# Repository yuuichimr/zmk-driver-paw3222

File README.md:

# ZMK PAW3222 Driver

This driver enables the use of the PIXART PAW3222 optical sensor with the ZMK framework.

## Overview

The PAW3222 is a low-power optical mouse sensor suitable for tracking applications such as mice and trackballs. This driver communicates with the PAW3222 sensor via SPI interface.

## Installation

1. Add as a ZMK module in your west.yml:

```
manifest:
  remotes:
    - name: zmkfirmware
      url-base: https://github.com/zmkfirmware
    - name: sekigon-gonnoc
      url-base: https://github.com/sekigon-gonnoc
  projects:
    - name: zmk
      remote: zmkfirmware
      revision: main
      import: app/west.yml
    - name: zmk-driver-paw3222
      remote: sekigon-gonnoc
      revision: main
```

## Device Tree Configuration

Configure in your shield or board config file (.overlay or .dtsi):

```dts
&pinctrl {
    spi0_default: spi0_default {
        group1 {
            psels = <NRF_PSEL(SPIM_SCK, 0, 12)>,
                <NRF_PSEL(SPIM_MOSI, 1, 9)>,
                <NRF_PSEL(SPIM_MISO, 1, 9)>;
        };
    };

    spi0_sleep: spi0_sleep {
        group1 {
            psels = <NRF_PSEL(SPIM_SCK, 0, 12)>,
                <NRF_PSEL(SPIM_MOSI, 1, 9)>,
                <NRF_PSEL(SPIM_MISO, 1, 9)>;
            low-power-enable;
        };
    };
};

&spi0 {
    status = "okay";
    compatible = "nordic,nrf-spim";
    pinctrl-0 = <&spi0_default>;
    pinctrl-1 = <&spi0_sleep>;
    pinctrl-names = "default", "sleep";
    cs-gpios = <&gpio0 13 GPIO_ACTIVE_LOW>;

    trackball: trackball@0 {
        status = "okay";
        compatible = "pixart,paw3222";
        reg = <0>;
        spi-max-frequency = <2000000>;
        irq-gpios = <&gpio0 15 GPIO_ACTIVE_LOW>;
    };
};
```

## Enable the module in your keyboard's Kconfig file

Add the following to your keyboard's `Kconfig.defconfig`:

```kconfig
if ZMK_KEYBOARD_YOUR_KEYBOARD

config ZMK_POINTING
    default y

config PAW3222
    default y

endif
```

## Properties

- `irq-gpios`: GPIO connected to the motion pin (required)
- `power-gpios`: GPIO that switches the sensor supply (optional)
- `res-cpi`: CPI resolution for the sensor (optional)
- `force-awake`: Initialize the sensor in "force awake" mode (optional, boolean)

## Kconfig

- `CONFIG_PAW3222_POLL_INTERVAL_MS` (default `15`, range 4-50): polling interval used
  while the sensor keeps reporting motion. Lower = smoother cursor, slightly more current.

## Notes

- Works with `CONFIG_PM_DEVICE_RUNTIME=y`: the driver takes a runtime-PM reference
  at init, so the sensor is no longer left suspended (previously it never reported
  motion when runtime PM was enabled).

## Example keyboard

[`keyboard/`](keyboard/) contains **Tsumugi**, an open low-profile wireless split
keyboard with a PAW3222 trackball built on this driver (PCB, case, ZMK firmware).

---

# ZMK PAW3222 ドライバ

このドライバは、PIXART PAW3222光学センサーをZMKフレームワークで使用できるようにします。

## 概要

PAW3222は、マウスやトラックボールなどのトラッキングアプリケーションに適した低消費電力の光学マウスセンサーです。このドライバはSPIインターフェースを介してPAW3222センサーと通信します。

## インストール

1. ZMKモジュールとして追加：

```
# west.yml に追加
manifest:
  remotes:
    - name: zmkfirmware
      url-base: https://github.com/zmkfirmware
    - name: sekigon-gonnoc
      url-base: https://github.com/sekigon-gonnoc
  projects:
    - name: zmk
      remote: zmkfirmware
      revision: main
      import: app/west.yml
    - name: zmk-driver-paw3222
      remote: sekigon-gonnoc
      revision: main
```

## デバイスツリー設定

シールドまたはボード設定ファイル（.overlayまたは.dtsi）で設定：

```dts
&pinctrl {
    spi0_default: spi0_default {
        group1 {
            psels = <NRF_PSEL(SPIM_SCK, 0, 12)>,
                <NRF_PSEL(SPIM_MOSI, 1, 9)>,
                <NRF_PSEL(SPIM_MISO, 1, 9)>;
        };
    };

    spi0_sleep: spi0_sleep {
        group1 {
            psels = <NRF_PSEL(SPIM_SCK, 0, 12)>,
                <NRF_PSEL(SPIM_MOSI, 1, 9)>,
                <NRF_PSEL(SPIM_MISO, 1, 9)>;
            low-power-enable;
        };
    };
};

&spi0 {
    status = "okay";
    compatible = "nordic,nrf-spim";
    pinctrl-0 = <&spi0_default>;
    pinctrl-1 = <&spi0_sleep>;
    pinctrl-names = "default", "sleep";
    cs-gpios = <&gpio0 13 GPIO_ACTIVE_LOW>;

    trackball: trackball@0 {
        status = "okay";
        compatible = "pixart,paw3222";
        reg = <0>;
        spi-max-frequency = <2000000>;
        irq-gpios = <&gpio0 15 GPIO_ACTIVE_LOW>;
    };
};
```

## キーボードのKconfigファイルでモジュールを有効化

キーボードの `Kconfig.defconfig` に以下を追加：

```kconfig
if ZMK_KEYBOARD_YOUR_KEYBOARD

config ZMK_POINTING
    default y

config PAW3222
    default y

endif
```

## プロパティ

- `irq-gpios`: モーションピンに接続されたGPIO（必須）
- `power-gpios`: センサー電源を切り替えるGPIO（任意）
- `res-cpi`: センサーのCPI解像度（任意）
- `force-awake`: センサーを「強制起動」モードで初期化（任意、ブール値）

## Kconfig

- `CONFIG_PAW3222_POLL_INTERVAL_MS`（既定 `15`、4〜50）: 動き検出中のポーリング間隔。
  小さいほどカーソルが滑らかになり、消費電流はわずかに増えます。

## 補足

- `CONFIG_PM_DEVICE_RUNTIME=y` でも動作します。初期化時にランタイムPMの参照を取得するため、
  以前のように「ランタイムPM有効時にセンサーがサスペンドされたまま動かない」問題は起きません。

## 作例キーボード

[`keyboard/`](keyboard/) に、このドライバを使ったロープロファイル無線分割トラックボールキーボード
**Tsumugi（紡）** の設計一式（PCB・ケース・ZMKファームウェア）があります。

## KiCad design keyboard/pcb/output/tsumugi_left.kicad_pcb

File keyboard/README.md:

# Tsumugi（紡）— ロープロファイル無線分割トラックボールキーボード

> **紡（つむぎ）**: 左右ふたつの手を、ひとつのキーボードへ「紡ぐ」。
> 分割にも一体型にもなり、ボール・トラックパッド・エンコーダー・ブランクを自由に差し替えられる。

Tsumugi は、moNa2 / roBa / Keyball44 / 小人キー / 双掌（SO-SHO）/ Toucan / torabo-tsuki など、
いま手に入る「トラックボール付き分割キーボード」の良いところを整理し、
それぞれの弱点をまとめて解消することを目標に設計した **オープンソースの分割キーボード** です。
PCB・ケース・ファームウェア・キーマップ・製造データまで、すべてこのディレクトリから再生成できます。

> ⚠️ **ステータス: 設計 v0.1（試作前）** — ファームウェアは全バリアントのビルド成功、
> PCB は KiCad DRC エラー 0 / 未配線 0 を確認済みですが、**実機はまだ製作・検証していません**。
> 「検証状況」の節を必ず読んでください。

---

## 1. 既存製品の整理（公開情報ベース）

| | moNa2 | roBa | Keyball44 | 小人キー | 双掌 SO-SHO | Toucan | torabo-tsuki LP | **Tsumugi** |
|---|---|---|---|---|---|---|---|---|
| キー数 | 42 | 42 | 44（MX） | 40 | 44 | 42 | S/M/L | **42 + ベイ押下 2** |
| ポインタ | 25mm ボール 右 | 34mm ボール | 34mm ボール | **19mm ボール 左右** | 34mm ボール/パッド | 40mm トラックパッド | 19/25mm ボール | **25/19mm ボール・23mm パッド、左右どちらにも** |
| ピッチ | 17mm | — | 19mm | **16mm** | — | 17mm | — | 18 × 17mm（Choc 標準キャップ） |
| 無線 | ZMK | ZMK | 有線 | ZMK | 無線 | ZMK | ZMK・乾電池 | **ZMK・LiPo 約1000mAh** |
| モジュール交換 | — | — | — | — | ◯ ボール/パッド/カバー | — | ボール位置調整 | **ボール / パッド / EC11 / ブランク** |
| テント | 別途 | 別途 | 別途 | **ケース単体で角度可変** | — | — | — | **一体テント：25mm球 9.5/14/18°、19mm球 6.5/9.5/14/18° から選んで印刷** |
| 表示 | LED | — | OLED | — | — | メモリ LCD | LED | RGB 状態 LED |
| 連結 | 背面マグネット | — | — | — | — | — | — | **内側マグネットで一体化** |

特に参考にした点と、Tsumugi での答え:

- **moNa2**: 完成度の高い薄型・軽量・無線。→ Tsumugi は薄さよりも**テント付きの姿勢**と**モジュール交換**を優先（外側は約14mmと低いが、内側はテントで32mmになる）。重さもケース約125g/片側（PLA中実換算）で、moNa2 の軽さには及ばない。
- **roBa / Keyball44**: 親指ボールの操作感の定番。→ 同じ「親指の休む位置にボール」配置を採用し、**ボールを持つ側を BLE セントラル**にして遅延を最小化。
- **双掌 SO-SHO**: 左右どちらにもモジュールを付けられる柔軟性。ただしボール装着時は約40mmと厚い。→ **25mmボール + 一体テントの空間にポッドを収める**ことで、平置きでも出っ張らない。
- **小人キー**: 左右 19mm デュアルボール、ケース単体でのテント角調整、16mm 狭ピッチ。→ **19mm ボールにも対応**し、テント角は複数の角度のケースから選んでプリントする方式に。デュアルボールは「左=スクロール専用」として取り込んだ。狭ピッチは Choc 標準キャップの入手性を優先して見送り（18×17mm）。
- **Toucan**: 40mm Cirque トラックパッドとメモリ LCD。→ ベイに Cirque トラックパッド（タップでクリック）を載せられるようにした。当初 35mm を狙ったが親指キーに 2.25mm 干渉したため、ベイに収まる最大径 27.9mm 以下の **23mm（TM023023）** を採用。表示は電池寿命を優先して RGB LED に留めた。
- **Charybdis / cocot46plus**: スクロール・精密（スナイプ）モードの定番化、cocot の「Lower 中はボールがスクロール」。→ `;` 長押し・**Lower 長押しのどちらでもスクロール**、`H` 長押しで精密モード。
- **torabo-tsuki**: PAW3222 による低消費電力。→ 同じ PAW3222 を採用し、**ドライバのランタイム電源管理バグを修正**（このリポジトリの `src/paw3222.c`）。

出典: [moNa2 (BOOTH)](https://booth.pm/ja/items/6376654) ・
[moNa2 レビュー](https://sensai-gadget.com/mona2-first-impression/) ・
[roBa (BOOTH)](https://booth.pm/ja/items/6010869) ・
[Keyball44 (遊舎工房)](https://shop.yushakobo.jp/products/8337) ・
[双掌 SO-SHO (エレキット)](https://www.elekit.co.jp/product/TH-601) ・
[torabo-tsuki LP (BOOTH)](https://booth.pm/ja/items/7200248) ・
[小人キー ビルドガイド](https://note.com/11_50iii/n/n75cff4d3502c) ・
[小人キー (BOOTH)](https://booth.pm/ja/items/7511676) ・
[Toucan (beekeeb)](https://beekeeb.com/toucan-keyboard/) ・
[Charybdis (Bastard Keyboards)](https://bastardkb.com/charybdis/) ・
[cocot46plus (遊舎工房)](https://shop.yushakobo.jp/en/products/6955)

## 2. Tsumugi が「超える」ためにやったこと

1. **ボール・トラックパッド・エンコーダー・ブランクを差し替えられる「モジュールベイ」を左右両方に**
   8ピンのベイコネクタ（GND / 3V3 / SCK・SCL / SDIO・SDA / NCS / MOTION・DR / COL / KEY）で、
   PAW3222 ボール（25/19mm）・Cirque 23mm トラックパッド（I2C）・EC11 エンコーダー（押し込みはマトリクスの1キー）・ブランクを交換可能。
   左にもボールかパッドを付ければ **左=専用スクロール、右=カーソル** のデュアル構成になる。
2. **一体型テント（9.5°）の中にボールポッドと大容量電池を収納**
   25mmボールとセンサーは深さが要るが、内側が高くなるテントの空間に収めることで、
   ケース底面は平らなまま・ボールが机に当たらない（センサー基板と机の隙間 2.4mm）。
   同じ空間に **803040（約1000mAh）** の LiPo が入る。一般的な XIAO 系キーボードの 110〜300mAh 級より大きい。
3. **マグネットで「Λ」型の一体型キーボードに**
   左右の内側エッジに磁石を埋め込み、くっつければ一体型テントキーボード、
   離せば普通の分割キーボード。持ち運び時も1つにまとまる。
4. **ボール側を BLE セントラルに**
   カーソルの動きが左右間の無線リンクを通らないので、遅延と取りこぼしが最小。
5. **マウス操作の作り込み（すべてメインライン ZMK 機能のみで実装）**
   - 自動マウスレイヤー（ボールを動かすとクリックキーが出現、打鍵直後は誤発動しない）
   - `;` 長押し、または Lower 長押し（cocot46plus 式）でボールがスクロールに、`H` 長押しで 1/3 速の精密モード
   - デュアルボール時は左ボールが常時スクロール（縦横）
   - フォークに依存しないため、ZMK 本体の更新に追従しやすい
6. **ZMK Studio 対応**（右側に書き込む）。Studio 上のキー配置は **PCB と同じ座標から自動生成**。
7. **単一の設計ソース**: ergogen の点群 → PCB / ケース / ZMK 物理レイアウト / キーマップ図 がすべて同じ座標から生成されるので、食い違いが起きない。
8. **再現可能な製造データ**: `tools/build_pcb.sh` 一発で ergogen → KiCad → 自動配線 → DRC → ガーバーまで生成。
9. **状態 LED（RGB）**: 起動時の電池残量、接続状態、低電圧警告（zmk-rgbled-widget）。
10. **電源**: センサー電源は nice!nano の外部電源スイッチ経由。ディープスリープ時は ZMK が遮断。

## 3. 仕様

| 項目 | 値 |
|---|---|
| 配列 | 3×6 カラムスタッガード + 親指 3 キー（左右）+ モジュールベイ |
| キー数 | 42（+ エンコーダー押し込み用ベイ接点 ×2） |
| キーピッチ | 18 × 17 mm（Choc スペーシング、MBK 等の Choc キーキャップ） |
| スイッチ | Kailh Choc v1（PG1350）ホットスワップ |
| コントローラ | nice!nano v2 互換（Pro Micro nRF52840） |
| ポインティング | PixArt PAW3222 + 25mm / 19mm ボール（3mm セラミックボール 3点支持）、または Cirque 23mm トラックパッド |
| 接続 | BLE（最大5台）+ USB-C、ZMK Studio |
| PCB | 2層 1.6mm、片側 140.3 × 96.5 mm、左右別基板 |
| ケース | 3Dプリント（サポート不要）、一体テント、マグネット連結。片側 144.8 × 101.9 mm、高さ 32.0mm（25mm球・9.5°）/ 24.4mm（19mm球・6.5°） |
| ベイのふた | 23mm トラックパッド / EC11 / ブランク（磁石で着脱、左右共通） |
| 電池 | LiPo 803040（8×30×40mm、約1000mAh）×2 |

### ピン配置（左右共通）

| nice!nano | nRF | 機能 | nice!nano | nRF | 機能 |
|---|---|---|---|---|---|
| D4 | P0.22 | ROW1 | D21 | P0.31 | COL1（内側） |
| D5 | P0.24 | ROW2 | D20 | P0.29 | COL2 |
| D6 | P1.00 | ROW3 | D19 | P0.02 | COL3 |
| D7 | P0.11 | ROW4（親指） | D18 | P1.15 | COL4 |
| D1 | P0.06 | ベイ SCK / ENC A | D15 | P1.13 | COL5 |
| D0 | P0.08 | ベイ SDIO / ENC B | D14 | P1.11 | COL6（外側） |
| D2 | P0.17 | ベイ NCS | D8 | P1.04 | LED 赤 |
| D3 | P0.20 | ベイ MOTION | D9 | P1.06 | LED 緑 |
| D10 | P0.09 | 予備 | D16 | P0.10 | LED 青 |

## 4. ディレクトリ構成

```
keyboard/
├── pcb/ergogen/           # 設計ソース（config.yaml + 自作フットプリント）
├── pcb/output/            # 生成物: KiCad PCB, DRC レポート, ガーバー zip, プレビュー画像
├── case/                  # ケース CAD（build123d）と STL/STEP、レンダリング
├── firmware/              # ZMK シールド定義、キーマップ、build.yaml
├── docs/                  # キーマップ図（SVG）
└── tools/                 # 生成パイプライン
    ├── build_pcb.sh       #   ergogen → KiCad → Freerouting → DRC → ガーバー
    ├── geometry.py        #   単一の形状ソース（PCB外形/ケース/レイアウト共用）
    ├── gen_zmk_layout.py  #   ZMK Studio 用物理レイアウト生成
    ├── build_firmware.sh  #   全ファームウェアバリアントのビルド
    └── draw_keymap.sh     #   キーマップ図の生成
```

## 5. ファームウェア

`firmware/build.yaml` のバリアント（GitHub Actions `Tsumugi firmware` で自動ビルド）:

| ファイル | 書き込む側 | 構成 |
|---|---|---|
| `tsumugi_right_ball.uf2` | 右 | **標準**: 右ボール（セントラル、ZMK Studio 有効） |
| `tsumugi_left_blank.uf2` | 左 | 左ベイ = ブランク |
| `tsumugi_left_encoder.uf2` | 左 | 左ベイ = EC11 エンコーダー（音量、レイヤーで曲送り/ページ送り） |
| `tsumugi_left_scrollball.uf2` + `tsumugi_right_ball_dual.uf2` | 左 + 右 | デュアルボール（左=スクロール専用） |
| `tsumugi_left_scrollpad.uf2` + `tsumugi_right_ball_dual.uf2` | 左 + 右 | 左トラックパッド=スクロール、右ボール=カーソル |
| `tsumugi_right_trackpad.uf2` | 右 | 右ベイ = 23mm トラックパッド（カーソル、タップでクリック） |
| `settings_reset.uf2` | 両方 | 設定リセット |

ローカルビルド:

```sh
# west ワークスペースと Zephyr SDK 0.17 を用意した上で
ZMK_APP=/path/to/zmk/app EXTRA_MODULES=/path/to/zmk-rgbled-widget keyboard/tools/build_firmware.sh
```

レイヤー: `Base` / `Lower`（数字・記号）/ `Raise`（ナビ・F キー）/ `Adjust`（Lower+Raise：BT・USB/BLE 切替・ブートローダー）/
`Mouse`（自動）/ `Scroll` / `Snipe`。コンボ: `Q+W`=Esc、`F+J`=Caps Word。
親指の `LANG2`/`LANG1` は英数/かな（タップ）、ホールドでレイヤー。

> センサーの取り付け向きで X/Y の向きが変わります。実機で逆になったら
> `firmware/config/tsumugi.keymap` の `&cursor_listener` に
> `<&zip_xy_transform (INPUT_TRANSFORM_X_INVERT | INPUT_TRANSFORM_Y_INVERT)>` などを追加してください。

## 6. PCB

```sh
keyboard/tools/build_pcb.sh   # 要: node, ergogen 4.2.1, KiCad 7, Java 21, freerouting 2.1
```

- 出力: `pcb/output/tsumugi_{left,right}.kicad_pcb`、`tsumugi_{left,right}_gerbers.zip`（JLCPCB 等にそのまま入稿可能な構成）、`drc_{left,right}.txt`
- 右基板は nice!nano を**裏返し**で実装します（ピン列をキー側に向けるため。ファームウェアのピン定義は左右共通）。
- 設計ルール: 配線 0.25mm / クリアランス 0.2mm / ビア 0.6/0.3mm / 基板端 0.3mm、両面 GND ベタ
- ergogen の出力外形は壊れた円弧を含むため、`geometry.py` が shapely で外形を作り直しています。

## 7. 部品表（片側 ×2 ではなく、キーボード1台分）

| 部品 | 数量 | 備考 |
|---|---|---|
| PCB（左・右） | 各1 | 2層 1.6mm |
| nice!nano v2 互換（Pro Micro nRF52840） | 2 | 左は部品面を上、**右は部品面を下（裏返し）**に実装。右は約2mmのスペーサー付きピンで |
| Kailh Choc v1 スイッチ | 42 | |
| Choc ホットスワップソケット（PG1350） | 42 | |
| ダイオード 1N4148W（SOD-123） | 44 | 各キー + ベイ押し込み |
| スライドスイッチ MSK-12C02 | 2 | 電源 |
| タクトスイッチ（TL3342 系 SMD） | 2 | リセット（底面から押す） |
| 0603 LED 赤/緑/青 + 0603 抵抗 1kΩ | 各2組 | 状態表示 |
| LiPo 電池 803040（約1000mAh） | 2 | ケースの電池ポケット 31×41×8.5mm |
| PAW3222 センサーモジュール（レンズ付き） | 1〜2 | ベイ接続。ピン配置はベイコネクタに合わせて配線 |
| 25mm または 19mm ボール | 1〜2 | 19mm はテントを 6.5° まで下げられる |
| 3mm セラミックボール（Si3N4/ZrO2） | 3〜6 | ボール支持 |
| EC11 エンコーダー + ノブ | 0〜1 | エンコーダー構成時 |
| Cirque TM023023（23mm トラックパッド） | 0〜2 | トラックパッド構成時。I2C モード（R1 抵抗を外す）で使用 |
| 1×8 ピンヘッダ（2.54mm） | 2 | ベイコネクタ |
| M2 ねじ + M2 インサート | 10 | ケース固定 |
| 6×3mm ネオジム磁石 | 4 | 左右連結 |
| 5×2mm ネオジム磁石 | 2 + ふた1枚につき2 | ベイのふたの固定 |
| Choc キーキャップ | 42 | |

## 8. 検証状況（正直な現状）

| 項目 | 状態 |
|---|---|
| ZMK ファームウェア 8 バリアント | ✅ ローカルと GitHub Actions でビルド成功（ZMK main / Zephyr 4.1, nice_nano） |
| PAW3222 ドライバ修正 | ✅ `CONFIG_PM_DEVICE_RUNTIME=y` でもコンパイル確認。実機での動作は未確認 |
| PCB 左・右 | ✅ 自動配線後の KiCad DRC エラー 0、未接続 0（残りはライブラリ参照・シルク重なり等の警告のみ） |
| ケース | ✅ 左右とも水密 STL・単一ボディ、机面より下にはみ出さない、部品同士の干渉ゼロをモデル上で確認。スライサー・試し刷りは未実施。部品実寸（USB-C、スペーサー付き nice!nano、J1 ヘッダ）との照合は未検証 |
| ケースの既知の課題 | ⚠️ 右ポッドに肉厚 0.4mm の箇所が1か所ある（試作前に要修正）。EC11 の回り止め溝の位置は未確認。エンコーダーのふたを使うときはセンサーモジュールを外す |
| 実機試作・打鍵感・ボール操作感・電池寿命 | ❌ 未検証（試作が必要） |
| PAW3222 モジュールのレンズ距離・ピン配置 | ❌ 使うモジュールに合わせた確認が必要 |

## 9. ロードマップ

1. v0.1 基板を発注（左右 各5枚）→ 組み立て → キースキャン・センサー・BLE の動作確認
2. ボール高さ・ベアリング位置・テント角を実測で調整（`case/case.py` のパラメータ）。J1 は通常高さのピンヘッダだと MCU カバーに当たるので、低背ヘッダかケーブル直付けにする
3. 電池寿命の実測と `CONFIG_PAW3222_POLL_INTERVAL_MS`・スリープ時間の最適化
4. v0.2: 実測を反映、ドングル構成（3台目の nRF52840 をセントラルに）への対応

## ライセンス

リポジトリの `LICENSE`（Apache-2.0）に従います。

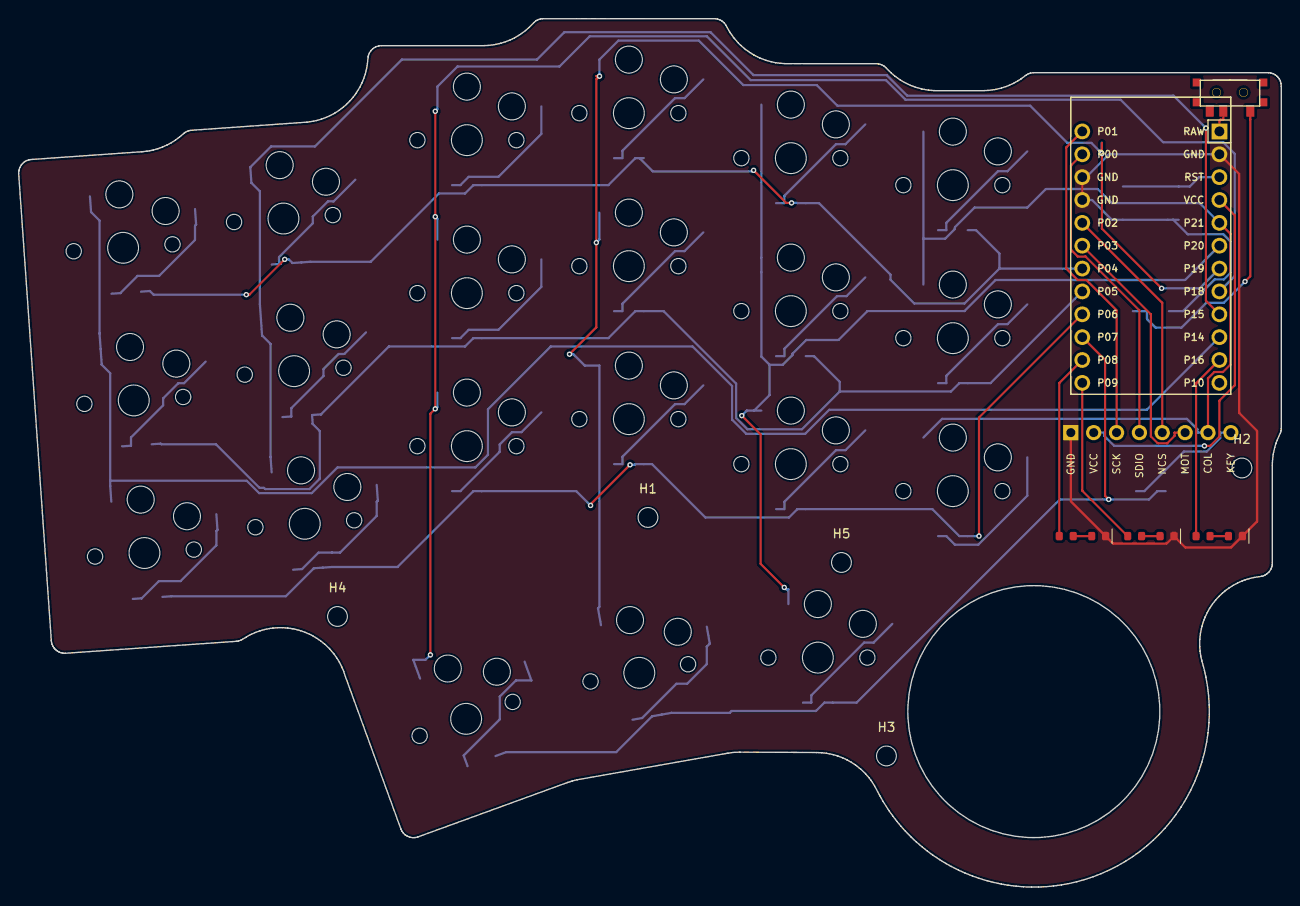
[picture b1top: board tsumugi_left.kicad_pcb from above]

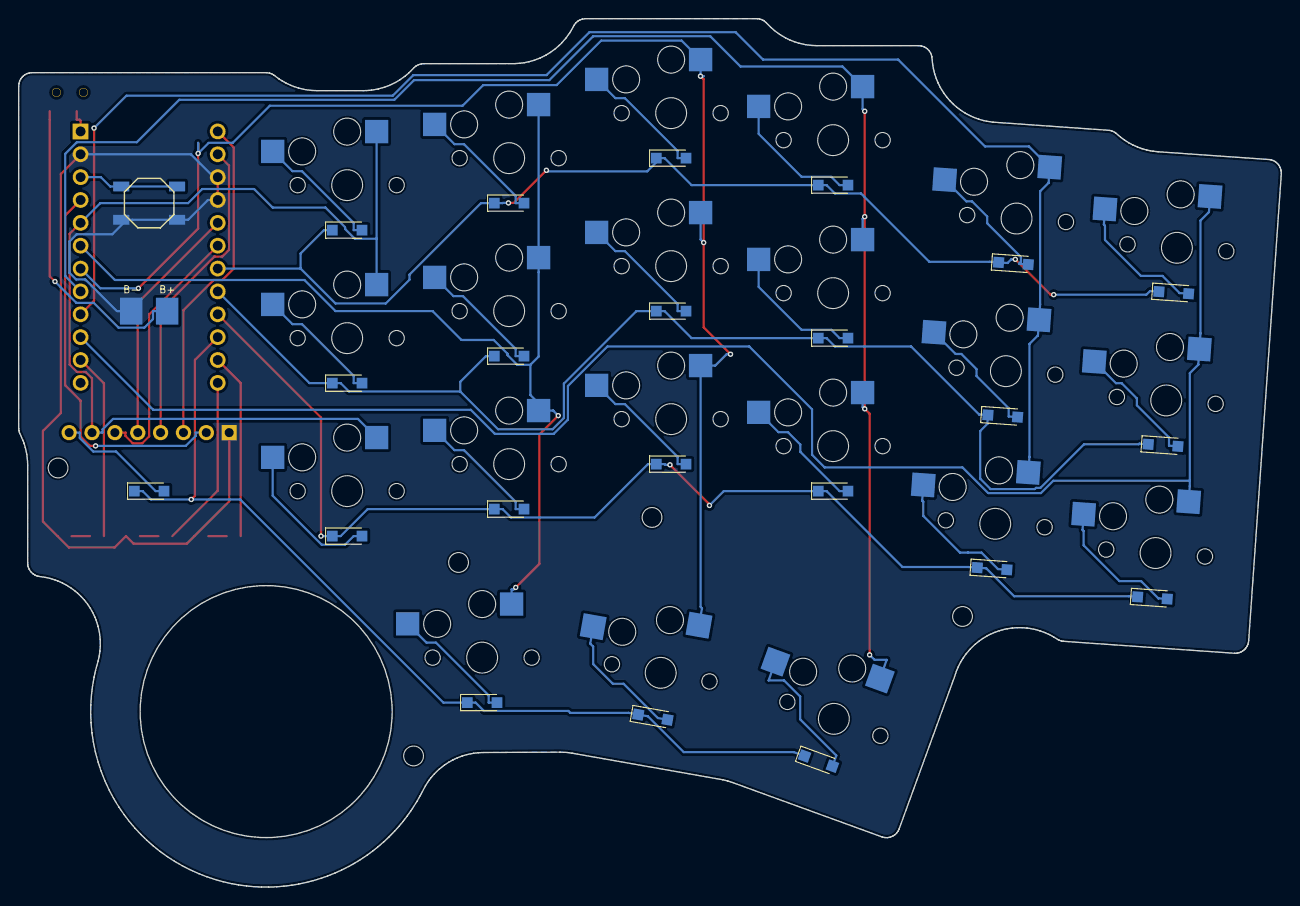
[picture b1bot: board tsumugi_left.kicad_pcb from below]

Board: 2 copper layers, 140.3 x 96.5 mm, 56 parts (23 on the bottom side), 47 nets.

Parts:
B1: SW_TACT_ALPS_SKQGABE010
BT1: BATTERY_PADS
D1, D2, D3, D4, D5, D6, D7, D8, D9, D10, D11, D12, D13, D14, D15, D16, D17, D18, D19, D20, D21, D22: 1N4148W; D_SOD-123_Back
H1, H2, H3, H4, H5: MountingHole_2.2mm_M2
J1: MODULE_BAY; MODULE_BAY_1x08
LED1, LED2, LED3: LED_R_0603_pair
MCU1: ProMicro
S1, S2, S3, S4, S5, S6, S7, S8, S9, S10, S11, S12, S13, S14, S15, S16, S17, S18, S19, S20, S21: PG1350
T1: SPDT_C128955

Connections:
BAT_P: BT1.1, T1.1
C1: J1.7, MCU1.5, S16.1, S17.1, S18.1
C2: MCU1.6, S13.1, S14.1, S15.1, S19.1
C3: MCU1.7, S10.1, S11.1, S12.1, S20.1
C4: MCU1.8, S7.1, S8.1, S9.1, S21.1
C5: MCU1.9, S4.1, S5.1, S6.1
C6: MCU1.10, S1.1, S2.1, S3.1
GND: B1.2, BT1.2, J1.1, LED1.4, LED2.4, LED3.4, MCU1.2, MCU1.15, MCU1.16
LED_B: LED3.1, MCU1.11
LED_B_A: LED3.2, LED3.3
LED_G: LED2.1, MCU1.24
LED_G_A: LED2.2, LED2.3
LED_R: LED1.1, MCU1.23
LED_R_A: LED1.2, LED1.3
MOD_KEY: D22.2, J1.8
MOD_MOTION: J1.6, MCU1.18
MOD_NCS: J1.5, MCU1.17
MOD_SCK: J1.3, MCU1.13
MOD_SDIO: J1.4, MCU1.14
R1: D3.1, D6.1, D9.1, D12.1, D15.1, D18.1, MCU1.19
R2: D2.1, D5.1, D8.1, D11.1, D14.1, D17.1, MCU1.20
R3: D1.1, D4.1, D7.1, D10.1, D13.1, D16.1, MCU1.21
R4: D19.1, D20.1, D21.1, D22.1, MCU1.22
RAW: MCU1.1, T1.2
RST: B1.1, MCU1.3
VCC: J1.2, MCU1.4
far_cluster: D21.2, S21.2
index_bottom: D13.2, S13.2
index_home: D14.2, S14.2
index_top: D15.2, S15.2
inner_bottom: D16.2, S16.2
inner_home: D17.2, S17.2
inner_top: D18.2, S18.2
mid_cluster: D20.2, S20.2
middle_bottom: D10.2, S10.2
middle_home: D11.2, S11.2
middle_top: D12.2, S12.2
near_cluster: D19.2, S19.2
outer_bottom: D1.2, S1.2
outer_home: D2.2, S2.2
outer_top: D3.2, S3.2
pinky_bottom: D4.2, S4.2
pinky_home: D5.2, S5.2
pinky_top: D6.2, S6.2
ring_bottom: D7.2, S7.2
ring_home: D8.2, S8.2
ring_top: D9.2, S9.2

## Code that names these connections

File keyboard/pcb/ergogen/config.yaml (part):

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        what: slider
        where: [[mcu, "-/^mirror_/"]]
        adjust:
          shift: [8.8, 18.3]   # top edge, next to USB-C and the RAW pin
        params:
          side: F
          from: BAT_P
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        adjust:
          shift: [-7.6, -31]
        params:
          gpio: LED_R
          mid: LED_R_A
      led_g:
        what: led_res
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        adjust:
          shift: [0, -31]
        params:
          gpio: LED_G
          mid: LED_G_A
      led_b:
        what: led_res
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        adjust:
          shift: [7.6, -31]
        params:
          gpio: LED_B
          mid: LED_B_A
  tsumugi_right:
    template: kicad5
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        adjust:
          shift: [-7.6, -31]
        params:
          gpio: LED_R
          mid: LED_R_A
      led_g:
        what: led_res
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        adjust:
          shift: [0, -31]
        params:
          gpio: LED_G
          mid: LED_G_A
      led_b:
        what: led_res
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        adjust:
          shift: [7.6, -31]
        params:
          gpio: LED_B
          mid: LED_B_A

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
